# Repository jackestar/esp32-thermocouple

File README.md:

<h3 align="center">ESP32-S2 Based Thermocouple Dirver</h3>

<div align="center">

</div>

### Materials

* ESP32-S2
* LM356
* AD620AN
* ~~LM35~~
* [TC33X-2-103E](https://componentsearchengine.com/part-view/TC33X-2-103E/Bourns) (or equivalent footprint)

### Proyect Structure

**IDF code**
FLAGS: 
 * TEST (breadboard/PCB)
 * DEBUG (SERIAL OUTPUT)

**Kicad**

> The last version is made for a 1-wire temperature module, the PCB can include LM35/LM335 like the example in [Commit 6ab5541](https://github.com/jackestar/esp32-thermocouple/commit/6ab55410f83fd76fe158129e17a911ef169d20fd)

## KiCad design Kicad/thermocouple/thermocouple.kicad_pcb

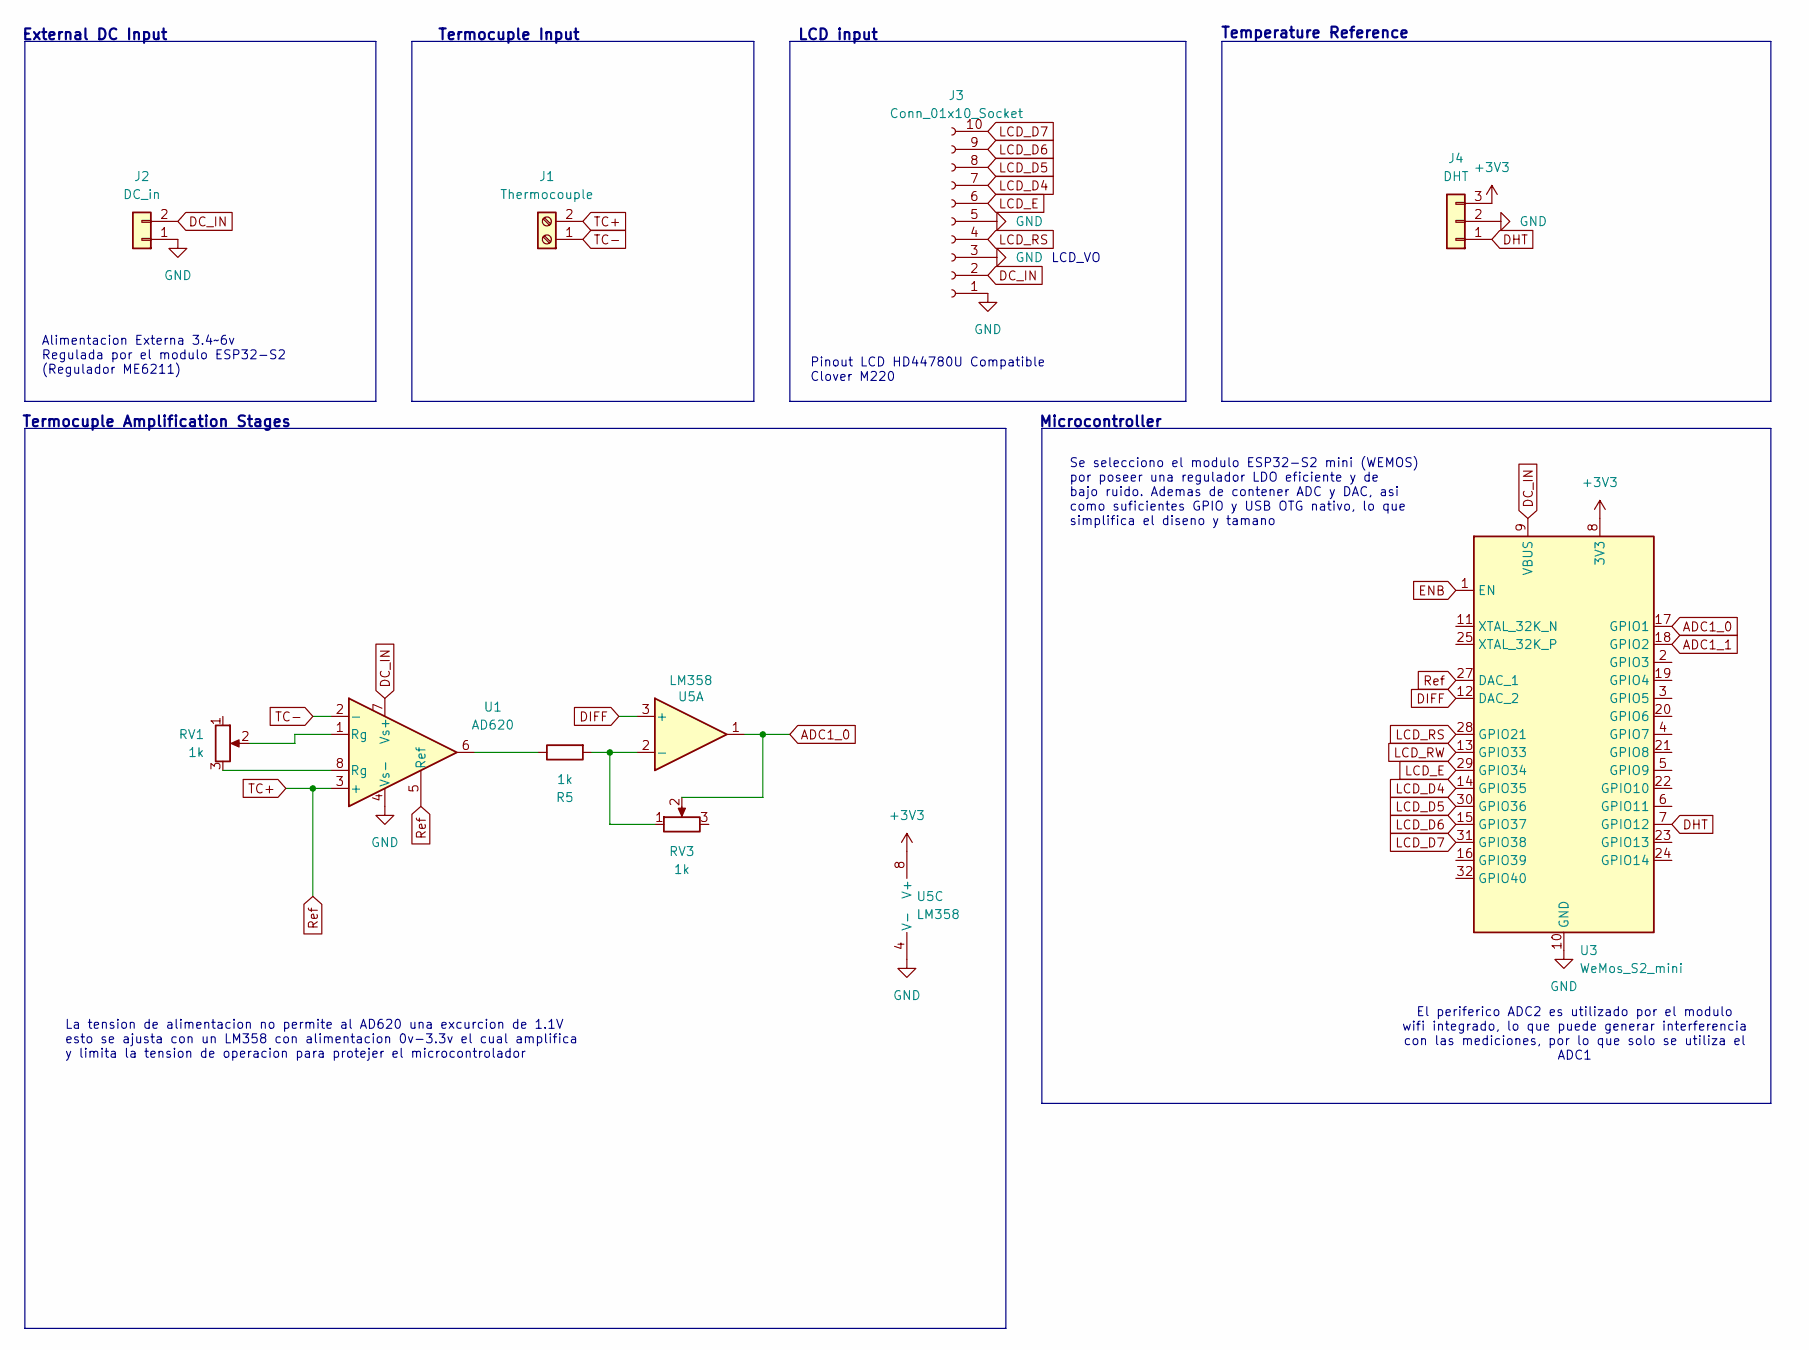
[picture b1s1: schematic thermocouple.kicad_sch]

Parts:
J1: Thermocouple; TerminalBlock_MaiXu_MX126-5.0-02P_1x02_P5.00mm
J2: DC_in; PinHeader_1x02_P2.54mm_Vertical
J3: Conn_01x10_Socket; PinSocket_1x10_P2.54mm_Vertical
J4: DHT; PinHeader_1x03_P2.54mm_Vertical
R5: 1k; R_1206_3216Metric_Pad1.30x1.75mm_HandSolder
RV1, RV3: 1k; Potentiometer_Bourns_TC33X_Vertical
U1: AD620; DIP-8_W7.62mm_Socket_LongPads
U3: WeMos_S2_mini; WEMOS_S2_mini
U5: LM358; SOIC-8_3.9x4.9mm_P1.27mm

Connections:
+3V3: J4.3, U3.8 (3V3), U5.8 (V+)
ADC1_0: RV3.2, U3.17 (GPIO1), U5.1
ADC1_1: U3.18 (GPIO2)
DC_IN: J2.2, J3.2, U1.7 (Vs+), U3.9 (VBUS)
DHT: J4.1, U3.7 (GPIO12)
DIFF: U3.12 (DAC_2), U5.3 (+)
ENB: U3.1 (EN)
GND: J2.1, J3.1, J3.3, J3.5, J4.2, U1.4 (Vs-), U3.10 (GND), U3.26 (GND), U5.4 (V-)
LCD_D4: J3.7, U3.14 (GPIO35)
LCD_D5: J3.8, U3.30 (GPIO36)
LCD_D6: J3.9, U3.15 (GPIO37)
LCD_D7: J3.10, U3.31 (GPIO38)
LCD_E: J3.6, U3.29 (GPIO34)
LCD_RS: J3.4, U3.28 (GPIO21)
LCD_RW: U3.13 (GPIO33)
unnamed: R5.1, U1.6
unnamed: RV1.2, U1.1 (Rg)
unnamed: RV1.3, U1.8 (Rg)
unnamed: R5.2, RV3.1, U5.2 (-)
Ref: J1.2, U1.3 (+), U1.5 (Ref), U3.27 (DAC_1)
TC-: J1.1, U1.2 (-)

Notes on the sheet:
Termocuple Input
LCD input
La tension de alimentacion no permite al AD620 una excurcion de 1.1V esto se ajusta con un LM358 con alimentacion 0v-3.3v el cual amplifica y limita la tension de operacion para protejer el microcontrolador
Se selecciono el modulo ESP32-S2 mini (WEMOS) por poseer una regulador LDO eficiente y de bajo ruido. Ademas de contener ADC y DAC, asi como suficientes GPIO y USB OTG nativo, lo que simplifica el diseno y tamano
External DC Input
Microcontroller
Alimentacion Externa 3.4~6v Regulada por el modulo ESP32-S2 (Regulador ME6211)
LCD_VO
Termocuple Amplification Stages
Temperature Reference
Pinout LCD HD44780U Compatible Clover M220
El periferico ADC2 es utilizado por el modulo wifi integrado, lo que puede generar interferencia con las mediciones, por lo que solo se utiliza el ADC1

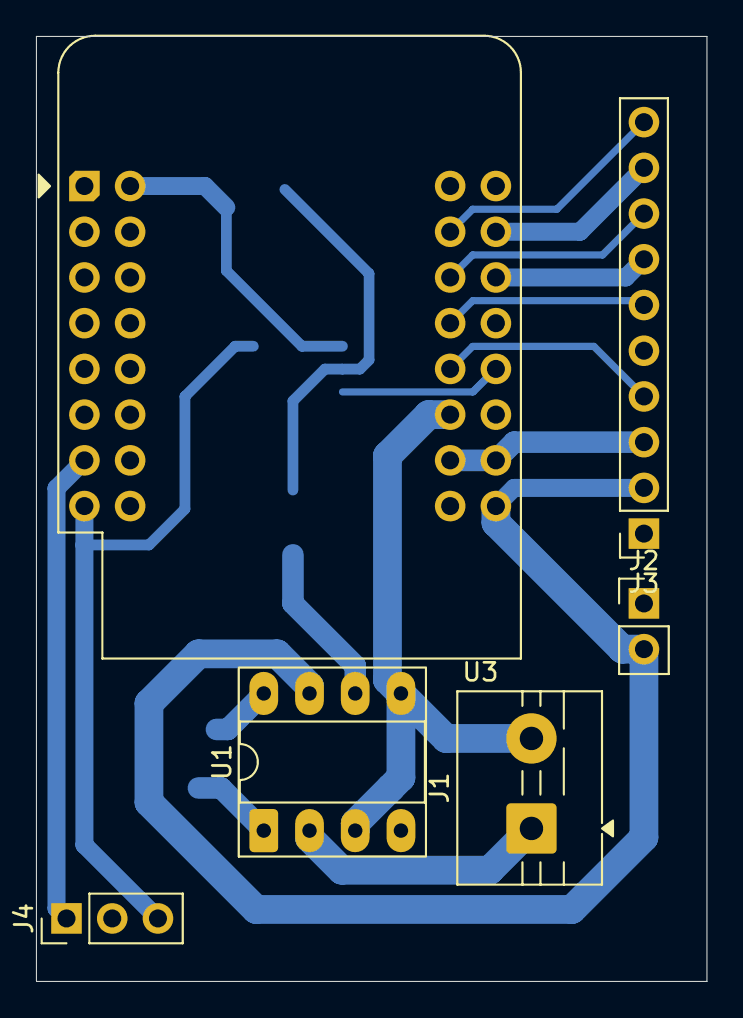
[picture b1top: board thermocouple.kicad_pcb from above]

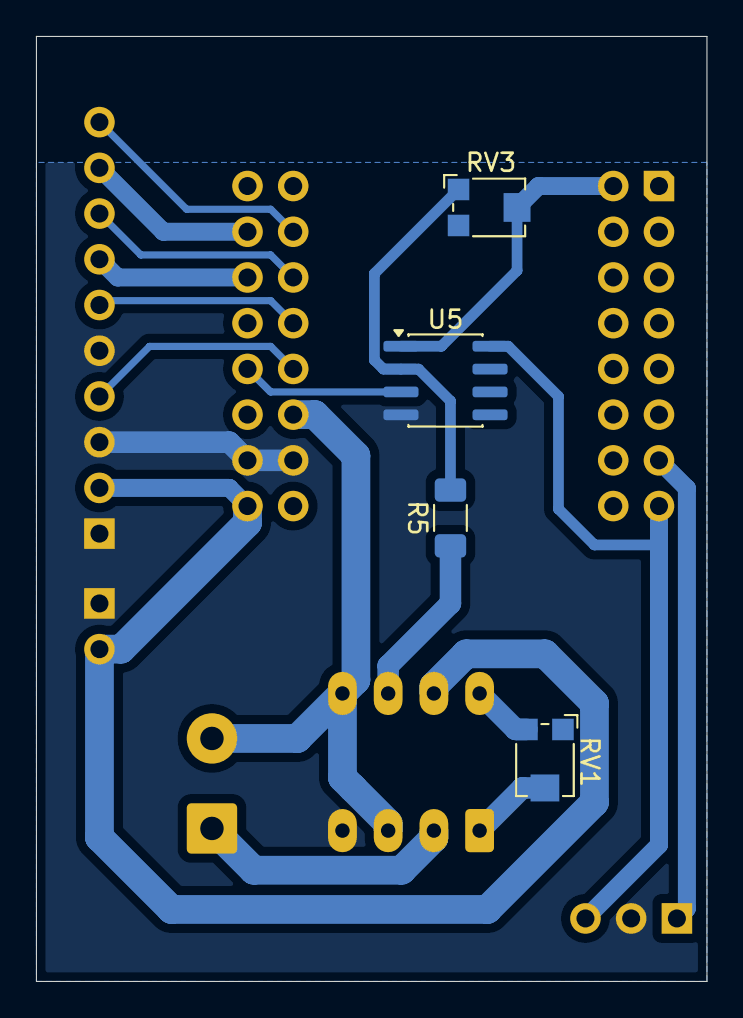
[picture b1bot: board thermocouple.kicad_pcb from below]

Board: 2 copper layers, 37.2 x 52.5 mm, 10 parts (4 on the bottom side), 18 nets.

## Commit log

2026-01-20 Code draft (without DAC)
2026-01-22 Added Kicad, fix some idf issues
2026-01-25 TestCircuit DAC configured
2026-01-31 Release Update readme Added wifi interface Add wifi UI Calibration Add DAC
